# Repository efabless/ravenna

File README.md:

# Ravenna

## Programming

To program the Ravenna EVB:

> pip3 install pyftdi
>
> cd firmware/<project>
>
> make flash

## Install Toolchain for Compiling Code

### For Mac

https://github.com/riscv/homebrew-riscv

### For Linux

https://github.com/riscv/riscv-gnu-toolchain

### Using install from PicoRV32

Get compiler toolchain for picorv32…
> % cd ~
>
> % git clone https://github.com/cliffordwolf/picorv32.git
>
> % cd picorv32
>
> % sudo apt-get install autoconf automake autotools-dev curl libmpc-dev \
libmpfr-dev libgmp-dev gawk build-essential bison flex texinfo \
gperf libtool patchutils bc zlib1g-dev git libexpat1-dev
>
> % make download-tools
>
> % make $(nproc) build-riscv32imc-tools
>
  
  To compile and download the firmware example code, first connect Ravenna 
  to your workstation using the USB cable.  No jumper should be installed on the board.
  
> % cd ravenna/firmware/blink
>
> % make clean
>
> % make hex
>
> % make flash

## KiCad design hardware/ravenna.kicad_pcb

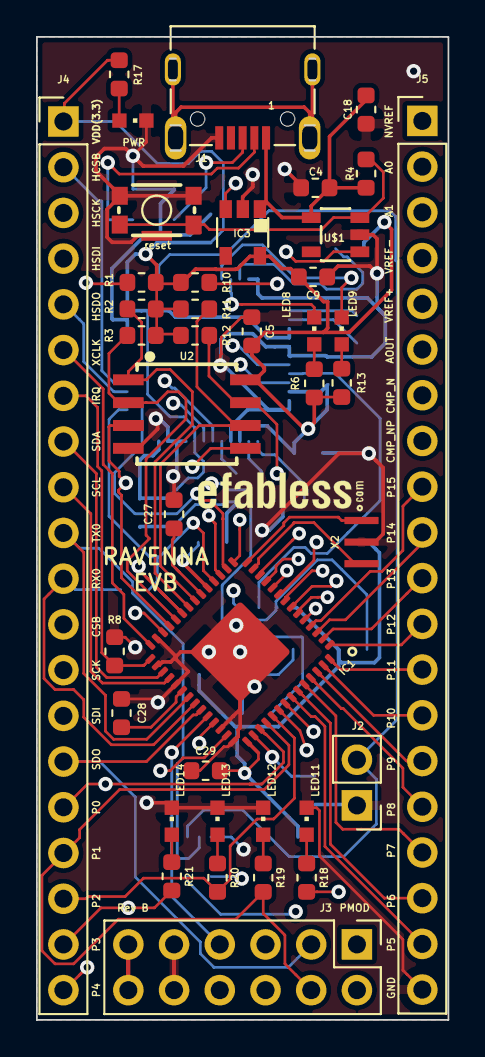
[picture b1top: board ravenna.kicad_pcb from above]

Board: 4 copper layers, 22.8 x 54.6 mm, 63 parts (0 on the bottom side), 77 nets.

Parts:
C4, C9, C18: 1uf; C_0603_1608Metric
C5, C8, C15, C16, C17, C19, C20, C21, C22, C27, C28, C29, C30: 0.1uf; C_0603_1608Metric
FUSE0, FUSE1: PGB10100603; 0603
IC1: RAVENAQFN56; QFN56
IC2: FT232H; LQFP48
IC3: MCP1755; SOT23-5
IC4: 93C56; SOT23-6
J1: 629105150521
J2: Conn_01x02_Male; PinHeader_1x02_P2.54mm_Vertical
J3: 2X6 FEMALE; PinHeader_2x06_P2.54mm_Vertical
J4, J5: CONN_20; PinHeader_1x20_P2.54mm_Vertical
LED8, LED9, LED10, LED11, LED12, LED13, LED14: LEDCHIPLED_0603; CHIPLED_0603
R1, R2, R3, R4, R5, R8, R10, R11, R12, R14, R15, R16, R23: 10K; R_0603_1608Metric
R6, R13, R17, R18, R19, R20, R21: 150; R_0603_1608Metric
R7: 2K 1%; R_0603_1608Metric
R9: 12K 1%; R_0603_1608Metric
R22: 0; R_0603_1608Metric
RESET1: SPST-SMD-4.6X2.8mm; TACTILE_SWITCH_SMD_4.6X2.8MM
U1: SN74LVC1G125DCKR; SC-70-5
U2: W25Q32FV; SOIC-8
U$1: MCP1316M; SOT23-5
X1: 12MHz; CSTNE12M0GH5L000R0
X2: 6 MHz; CSTNE12M0GH5L000R0

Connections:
+5V: C4.1, C18.1, IC3.1, J1.1, R4.2, U$1.4
/ANA_0: IC1.11, J5.2
/ANA_1: IC1.10, J5.3
/AOUT: IC1.7, J5.6
/COMP_INN: IC1.6, J5.7
/COMP_INP: IC1.5, J5.8
/HK_CSB: IC1.17, IC2.16, J4.2
/HK_SDO: IC1.15, IC2.15, J4.5
/I2C_SCL: IC1.32, J3.6, J4.9
/I2C_SDA: IC1.31, J3.8, J4.8
/IRQ: IC1.29, J4.7, R8.1
/NVREF: IC1.12, J5.1
/P0: IC1.45, J3.2, J4.16, R18.2
/P1: IC1.46, J3.4, J4.17, R19.2
/P2: IC1.47, J4.18, R20.2
/P3: IC1.48, J4.19, R21.2
/P4: IC1.49, J4.20
/P5: IC1.50, J5.19
/P6: IC1.51, J5.18
/P7: IC1.52, J5.17
/P8: IC1.53, J5.16
/P9: IC1.54, J5.15
/P10: IC1.55, J5.14
/P11: IC1.56, J5.13
/P12: IC1.1, J5.12
/P13: IC1.2, J5.11
/P14: IC1.3, J5.10
/P15: IC1.4, J5.9
/RAPTOR_CS: IC1.22, R2.2, U2.1
/RAPTOR_D0: IC1.23, R10.2, U2.5
/RAPTOR_D1: IC1.24, R3.2, U2.2
/RAPTOR_D2: IC1.25, R1.2, U2.3
/RAPTOR_D3: IC1.26, R12.2, U2.7
/RAPTOR_SCK: IC1.21, R11.2, U2.6
/RX0: IC1.36, J4.11, R22.2
/RXD_HK_SDI: IC1.16, IC2.14, J4.4, U1.4
/SPI_CSB: IC1.39, J3.1, J4.12
/SPI_SCK: IC1.38, J3.7, J4.13
/SPI_SDI: IC1.41, J3.5, J4.14
/SPI_SDO: IC1.37, J3.3, J4.15
/TX0: IC1.35, J4.10, U1.2
/TXD_EN: IC2.25, J2.2, R23.1, U1.1
/TXD_HK_SCK: IC1.18, IC2.13, J4.3, R22.1
/VREF+: IC1.8, J5.5
/VREF-: IC1.9, J5.4
/XCLK: IC1.28, J4.6
GND: C4.2, C5.1, C8.1, C9.2, C15.1, C16.2, C17.2, C18.2, C19.2, C20.2, C21.2, C22.1, C27.2, C28.1, C29.1, C30.2, FUSE0.1, FUSE1.1, IC1.27, IC1.30, IC1.33, IC1.40, IC1.42, IC1.EPAD, IC2.4, IC2.9, IC2.10, IC2.11, IC2.22, IC2.23, IC2.35, IC2.36, IC2.41, IC2.42, IC2.47, IC2.48, IC3.2, IC4.2, J1.5, J2.1, J3.9, J3.10, J5.20, LED10.C, LED11.C, LED12.C, LED13.C, LED14.C, R8.2, R9.1, RESET1.3, RESET1.4, RESET1.5, U1.3, U2.4, U$1.2, X1.2, X2.2
unnamed: C8.2, IC2.37
unnamed: C22.2, IC2.38
unnamed: C27.1, IC1.20
unnamed: C28.2, IC1.34
unnamed: C30.1, IC1.44
unnamed: FUSE0.2, IC2.7, J1.3
unnamed: FUSE1.2, IC2.6, J1.2
unnamed: IC1.13, X2.1
unnamed: IC1.14, X2.3
unnamed: IC2.1, X1.1
unnamed: IC2.2, X1.3
unnamed: IC2.5, R9.2
unnamed: IC2.32, LED9.C
unnamed: IC2.33, LED8.C
unnamed: IC2.34, R5.1
unnamed: IC2.43, IC4.1, R7.1, R16.2
unnamed: IC2.44, IC4.4, R14.2
unnamed: IC2.45, IC4.5, R15.2
unnamed: IC3.3, U$1.1
unnamed: IC4.3, R7.2
unnamed: J1.SHELL, J1.SHELL1, J1.SHELL2, J1.SHELL3
unnamed: LED8.A, R6.2
unnamed: LED9.A, R13.2
unnamed: LED10.A, R17.1
unnamed: LED11.A, R18.1
unnamed: LED12.A, R19.1
unnamed: LED13.A, R20.1
unnamed: LED14.A, R21.1
unnamed: R4.1, RESET1.1, RESET1.2, U$1.3
VDD: C5.2, C9.1, C15.2, C16.1, C17.1, C19.1, C20.1, C21.1, C29.2, IC1.19, IC1.43, IC2.3, IC2.8, IC2.12, IC2.24, IC2.39, IC2.40, IC2.46, IC3.5, IC4.6, J3.11, J3.12, J4.1, R1.1, R2.1, R3.1, R5.2, R6.1, R10.1, R11.1, R12.1, R13.1, R14.1, R15.1, R16.1, R17.2, R23.2, U1.5, U2.8

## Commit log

2020-01-30 added flash target to make
2020-01-30 add hkspi script
2020-01-31 ravenna_hkspi
2020-01-31 enhance blink led pattern
2020-02-07 added uart example
2020-02-07 clean up sections.lds and start.s
2020-02-07 uart - flush output
2020-02-24 uart - debug
2020-02-28 add clock test
2020-02-29 debug clock
2020-03-11 add startup_ravenna.tcl
2020-03-14 clock debug
2020-03-17 support for hkspi
2020-03-17 add hardware for pcba; gitignore
2020-03-17 parts libraries
2020-03-17 schematic review updates
2020-03-21 completed revised layout
2020-03-21 updated layout
2020-03-21 add gerbers; updated silkscreen
2020-03-22 fixed gnd pad for switch; fixed courtyard overlaps;
2020-03-24 uart debug
2020-04-08 add adc; gerber files updated
2020-04-08 update parts and footprints
2020-04-08 adc fix
2020-04-08 flash debug
2020-04-08 hkdebug script
2020-04-08 adc debug
2020-04-09 i2c test
2020-04-29 uart
2020-06-03 debug i2c; read data exec in mem function
2020-06-29 readme
2020-07-14 rtc firmware updates
2020-07-21 update rtc; add nvram; update hardware;
2020-09-05 added blink.hex
